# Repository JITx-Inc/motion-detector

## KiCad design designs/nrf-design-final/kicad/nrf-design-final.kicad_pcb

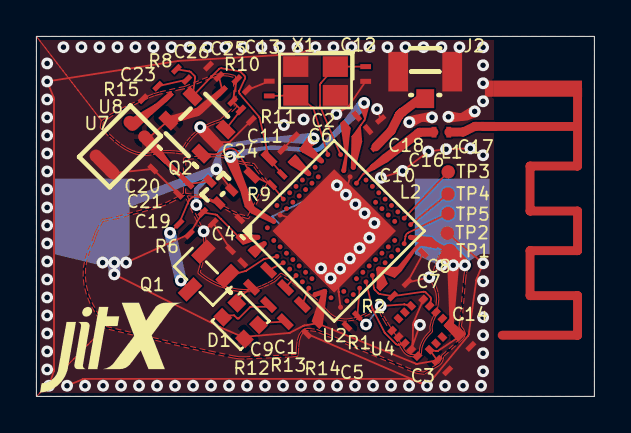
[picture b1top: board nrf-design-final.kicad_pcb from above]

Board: 2 copper layers, 31.0 x 20.0 mm, 54 parts (1 on the bottom side), 31 nets.

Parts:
ANT1: ANTENNA_2GHZ4_INVERTED_F_GEOMETRY
C1: 100n; Pkg0402_30
C2: 100p; Pkg0402_5
C3: 10u; Pkg0402_27
C4: 1u; Pkg0402_9
C5: 4.7u; Pkg0402_17
C6: 100n; Pkg0402_20
C7: 100n; Pkg0402_22
C8: 100n; Pkg0402_26
C9: 1u; Pkg0402_1
C10: 100n; Pkg0402_7
C11: 100n; Pkg0402_19
C12: 15p; Pkg0402_25
C13: 15p; Pkg0402_31
C14: 100n; Pkg0402
C16: 800f; Pkg0402_10
C17: 500f; Pkg0402_13
C18: 500f; Pkg0402_11
C19: 100n; Pkg0402_15
C20: 100n; Pkg0402_2
C21: 10n; Pkg0402_29
C23: 1u; Pkg0402_12
C24: 150p; Pkg0603_2
C25: 10n; Pkg0402_6
C26: 10u; Pkg0402_23
D1: LP_3
J1: LP_2
J2: LP_4
JITX1: JITX_SM_LP
L1: 4.7n; Pkg0402_18
L2: 4.7n; Pkg0402_14
Q1: LP
Q2: LP_1
R1, R2: 8K2; Pkg0402_3
R6: 1M; Pkg0402_8
R8: 1K5; Pkg0402_16
R9: 51K; Pkg0402_21
R10: 51K; Pkg0402_24
R11: 51K; Pkg0402_28
R12: 1K8; Pkg0603
R13: 1K8; Pkg0603_1
R14: 510R; Pkg0603_3
R15: 0R; Pkg0402_4
TP1, TP2, TP3, TP4, TP5: SMD_TESTPT
U2: LP_8
U4: XDCR_LIS3DHTR
U7: LP_6
U8: LP_5
X1: LP_7

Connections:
ANT: C16.1, L1.1, L2.1, U2.H23
Cin_p2: C23.2, R8.1
D: Q1.3, Q2.1, R6.2
DEC1: C1.1, U2.C1
DEC2: C11.1, U2.A18
DEC3: C2.1, U2.D23
DEC4: C4.1, C10.1, U2.B5, U2.E24
GND: ANT1.gnd, C1.2, C2.2, C3.2, C4.2, C5.2, C6.2, C7.2, C8.2, C9.2, C10.2, C11.2, C12.2, C13.2, C14.2, C16.2, C17.2, C18.2, C19.2, C20.2, C21.2, C25.2, C26.2, J1.2, J2.1, J2.3, Q1.2, R11.2, R15.2, TP2.p, U2.74, U2.AD2, U2.B7, U2.F23, U4.5, U4.10, U4.12, U7.2, U7.3, U8.2, X1.2, X1.4
I2C_scl: R2.1, U2.AD12, U4.4
I2C_sda: R1.1, U2.AD8, U4.6
L_p2: C18.1, J2.2, L2.2
VDD: C3.1, C5.1, C6.1, C7.1, C8.1, C9.1, C14.1, C19.1, D1.3, J1.1, J1.3, Q2.2, R1.2, R2.2, R6.1, TP1.p, U2.A22, U2.AD14, U2.AD23, U2.B1, U2.W1, U2.Y2, U4.1, U4.14
VDDA: C20.1, C21.1, C26.1, Q2.3, R10.1, U7.1, U8.5
WAKE: U2.AD10, U4.11
XC1: C12.1, U2.B24, X1.1
XC2: C13.1, U2.A23, X1.3
a: ANT1.launch, C17.1, L1.2
b: D1.2, R14.2
g: D1.4, R13.2
mcu_control-pins0_timer: R12.1, U2.J1
mcu_control-pins1_timer: R13.1, U2.N1
mcu_control-pins2_timer: R14.1, U2.U1
mcu_debug_swdclk: TP3.p, U2.AA24
mcu_debug_swdio: TP4.p, U2.AC24
mcu_debug_swo: TP5.p, U2.AD22
mcu_vdda-sw_gpio: Q1.1, U2.G1
op-: C24.1, R8.2, R9.1, U8.4
r: D1.1, R12.2
signal: C23.1, R15.1, U7.4
vout: C24.2, R9.2, U2.A10, U8.1
vref: C25.1, R10.2, R11.1, U8.3

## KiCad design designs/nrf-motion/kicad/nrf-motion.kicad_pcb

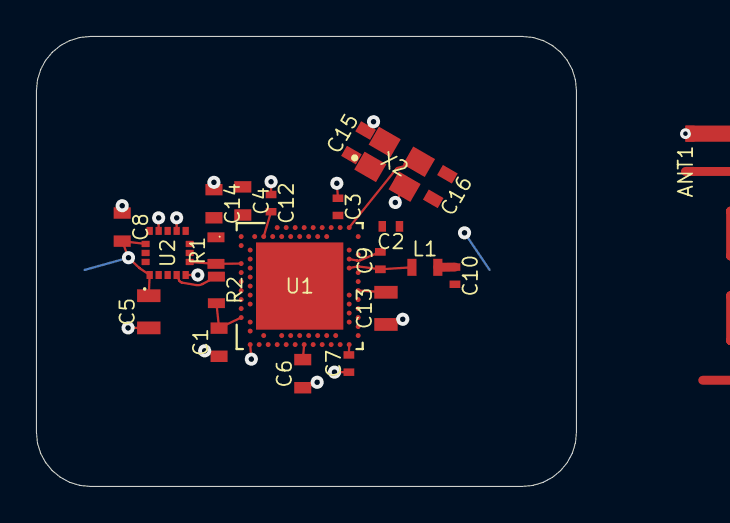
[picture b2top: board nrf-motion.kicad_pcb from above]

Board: 4 copper layers, 30.0 x 25.0 mm, 23 parts (1 on the bottom side), 13 nets.

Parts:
ANT1: ANT_2GHZ4_INVERTED_F_GEOM
BT1: BAT_SMD_BS_08_B2AA016
C1, C4, C6, C8, C14: 100n; Pkg0603_2
C2: 100p; Pkg0402
C3, C12: 1u; Pkg0402
C5: 10u; Pkg0805
C7: 4.7u; Pkg0402
C9: 800f; Pkg0402_1
C10: 500f; Pkg0402
C13: 820p; Pkg0805
C15, C16: 15p; Pkg0603
L1: 4.7n; Pkg0603_1
R1, R2: 8K2; Pkg0603_3
U1: XCVR_NRF52840_QIAA_R_PKG
U2: XDCR_LIS3DHTR
X2: XTAL_4_3225

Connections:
ANT: C9.1, L1.1, U1.H23
DEC1: C14.2, U1.C1
DEC3: C2.2, U1.D23
DEC4: C12.2, U1.B5, U1.E24
DEC5: C13.2, U1.N24
GND: ANT1.gnd, BT1.2, C1.1, C2.1, C3.1, C4.1, C5.1, C6.1, C7.1, C8.1, C9.2, C10.2, C12.1, C13.1, C14.1, C15.2, C16.2, U1.74, U1.AD2, U1.B7, U1.F23, U2.5, U2.10, U2.12, X2.2, X2.4
SDO: R1.1, U1.G1, U2.6
SPC: R2.1, U1.H2, U2.4
VDD: BT1.1, C1.2, C3.2, C4.2, C5.2, C6.2, C7.2, C8.2, R1.2, R2.2, U1.A22, U1.AD14, U1.AD23, U1.B1, U1.W1, U1.Y2, U2.1, U2.14
WAKE: U1.A14, U2.11
XC1: C15.1, U1.B24, X2.1
XC2: C16.1, U1.A23, X2.3
launch: ANT1.launch, C10.1, L1.2

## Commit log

2023-04-27 Broken stabilization
2023-04-28 Update antenna
2023-06-16 Pin assignment ratsnest locked
2023-07-07 Unable to reapply operations
2023-07-10 draft version:
2023-07-11 Updated to latest ocdb:dev
2023-07-12 Updated OCDB to include new amplifier filter design.
    This is a WIP and only intended to show circuit for bug report.
2023-07-20 WIP - Updated the design to include current changes.
2023-07-20 Added the designs folder changes so I have a starting point.
2023-07-24 Added initial documentation related to simulations.
    I've added:
    1. The python Z3 solver that was the basis for picking resistor values.
    2. Simulations in TINA that show the functional results for two OpAmps considered
    1. The MCP6001 was the existing whic I thought would have issues and the simulation bore this out.
    2. The TS971 - better opamp that meets performance requirements.
2023-07-29 Updated components used in this design
2023-07-29 Updated the physical design files as a checkpoint.
2023-07-29 Updated the main design file.
    This includes the amplifier updates and other changes now.
2023-07-29 Updated reference to OCDB submodule
2023-07-31 I wiped the design folder and started again. This is the schematic layout complete
    I haven't done the physical design yet.
2023-07-31 Updated OCDB
2023-07-31 Saving the state of the schematic after adding components for NRF MCU
2023-08-01 Saving the layout as a checkpoint.
2023-08-02 Added routed checkpoint
2023-08-02 Attempting to save more so my design updates in Windows properly.
2023-10-06 Arc error
2023-10-06 Dead topology
2023-10-10 Board routing with no visible components
2023-11-03 [Bugfix] Updated `parametric` -> `placeholder`
2023-11-03 Add BOM visualization code
2024-01-12 commented out antenna and references to it
2024-06-29 initial check-in for routed design
2024-06-29 added some missing traces and improved sch
2024-07-01 updated design with latest develop
2024-07-01 removed lock file
2024-07-02 check in for almost done kicad version
2024-07-03 check in before move of NRF
2024-07-03 removed cache from git
2024-07-03 stable design state, will now rm parts-db
2024-07-03 can't export design to Kicad
2024-07-03 smaller board
2024-07-05 swapped crystal
2024-07-05 new branch for BOM exploration
2024-07-08 new branch with full design plus bom test
2024-07-09 stage project
2024-07-10 checkpoint to verify Altium export
2024-07-17 fixed capitalization
2024-07-19 check-in for export
2024-07-19 exported kicad/altium
2024-07-19 improved schematic
2024-07-19 improved schematic some more
2024-07-22 fixed up warnings, 3D rotations
2024-07-22 finalizing design with kicad export
2024-07-24 fixed up schematic
2024-07-25 cleaning up design a bit more
2024-08-02 bring set-export-backend up
2024-08-06 using a better path for 3D models
2024-08-08 check in for debug
2024-08-09 latest code before PC xfer
2024-08-09 updated ocdb ref to 3.14.0
2024-08-09 removed local ocdb
2024-08-16 broken 3D export
2024-08-17 kicad export
2024-08-17 general checkin
2024-08-19 exportable version with 3d models
2024-08-19 with Kicad version
2024-08-20 updated with exported designs
2024-08-29 Update slm.toml to use ocdb from jitx-client using JITX-ROOT
2024-08-30 to check Altium export
2024-08-30 after Altium export
2024-09-04 drc results
2024-09-04 added some via connections
2024-09-09 with decent export
2024-09-09 added new files
2024-09-09 ignore cache dir
2024-09-10 check in on Windows with Altium export
2024-09-11 exported Altium for 3.16
2024-09-11 removing extraneous dirs
2024-09-11 updated ignored files
2024-09-12 latest altium export
2024-09-12 kicad edit of silkscreen
2024-09-16 altium better drc
2024-09-17 kicad update
2024-09-27 save non-introspected design
2024-09-27 cleaning up files
2024-09-28 check point commit
2024-09-30 kicad update issues
2024-10-02 trying to stabilize the BOM
2024-10-03 better versions
2024-10-17 use git in ocdb
2024-11-07 kicad save
2024-11-07 tweaked inductor val, removed commented out code
